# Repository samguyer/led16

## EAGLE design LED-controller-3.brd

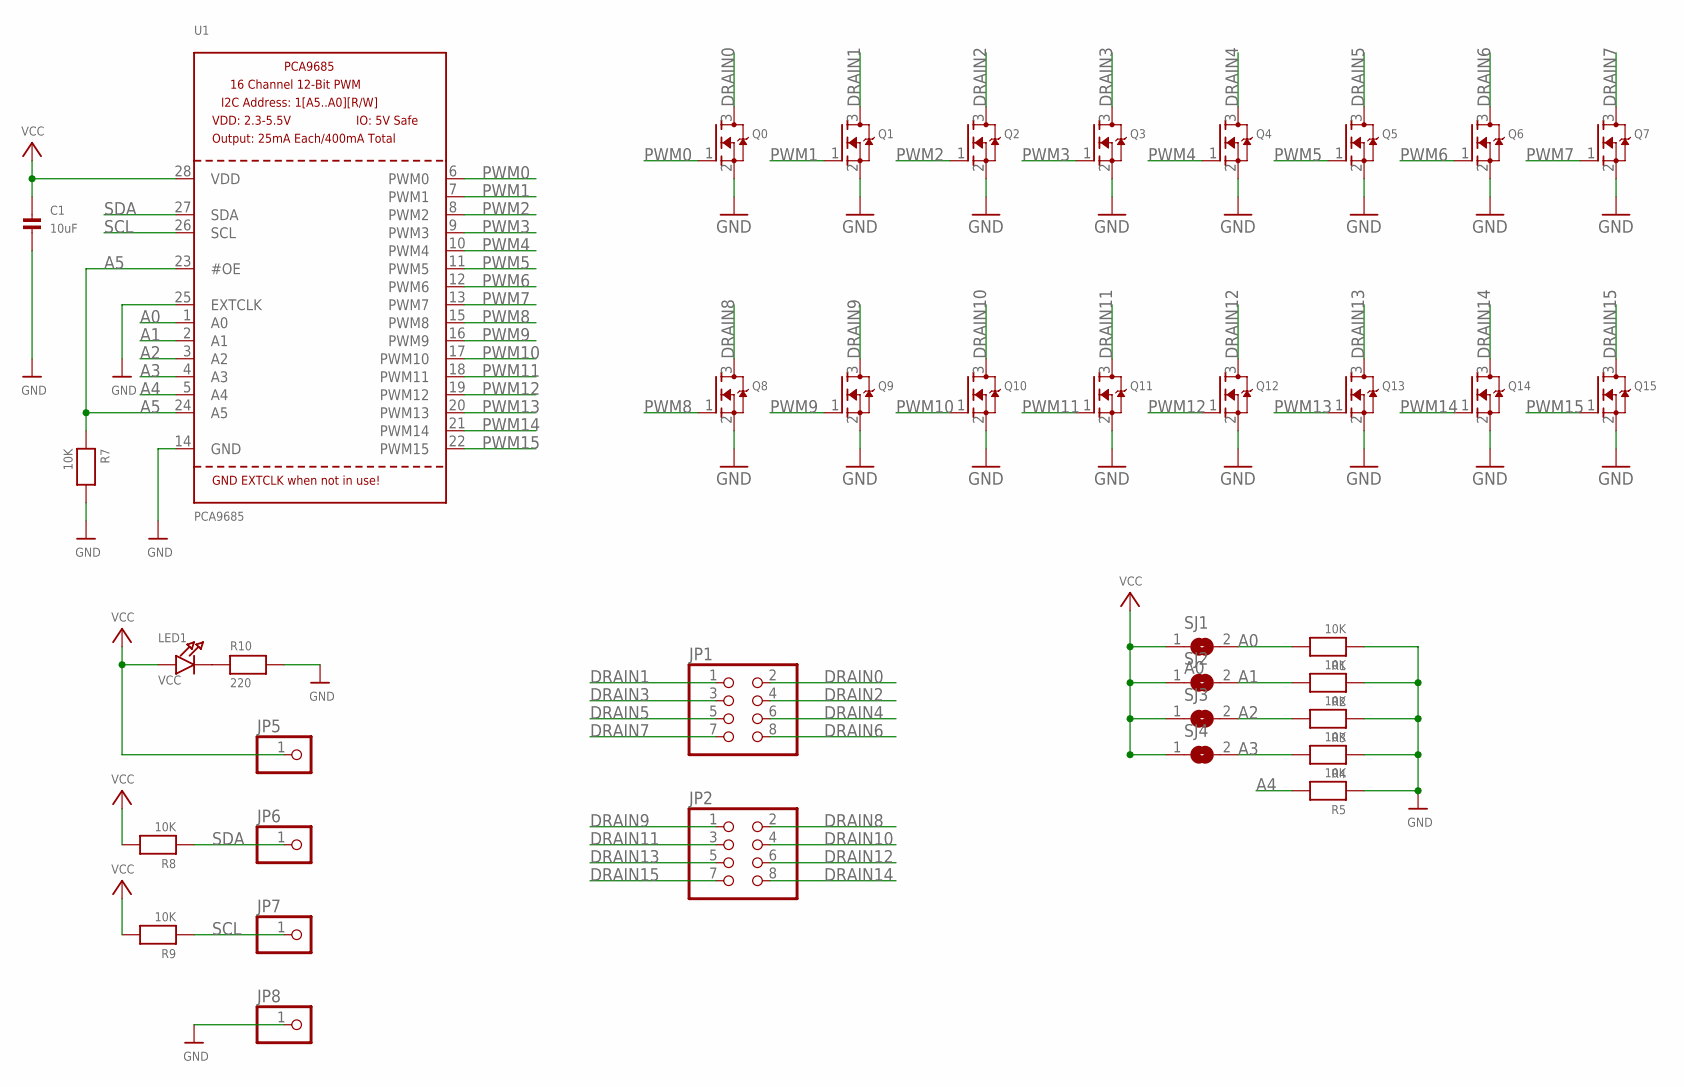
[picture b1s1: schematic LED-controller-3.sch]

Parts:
C1: 10uF; 0805
JP1, JP2: PINHD-2X4; 2X04
JP5, JP6, JP7, JP8: PINHD-1X1CB; 1X01-CLEANBIG
LED1: VCC; CHIPLED_0805
Q0, Q1, Q2, Q3, Q4, Q5, Q6, Q7, Q8, Q9, Q10, Q11, Q12, Q13, Q14, Q15: MOSFET-NREFLOW; SOT23
R1, R2, R3, R4, R5, R7, R8, R9: 10K; 0603
R10: 220; 0603
SJ1: A0; SJ
SJ2, SJ3, SJ4: SJ
U1: PCA9685; TSSOP28

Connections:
A0: R1.2, SJ1.2, U1.1 (A0)
A1: R2.2, SJ2.2, U1.2 (A1)
A2: R3.2, SJ3.2, U1.3 (A2)
A3: R4.2, SJ4.2, U1.4 (A3)
A4: R5.2, U1.5 (A4)
A5: R7.1, U1.23 (#OE), U1.24 (A5)
DRAIN0: JP1.2, Q0.3 (D)
DRAIN1: JP1.1, Q1.3 (D)
DRAIN2: JP1.4, Q2.3 (D)
DRAIN3: JP1.3, Q3.3 (D)
DRAIN4: JP1.6, Q4.3 (D)
DRAIN5: JP1.5, Q5.3 (D)
DRAIN6: JP1.8, Q6.3 (D)
DRAIN7: JP1.7, Q7.3 (D)
DRAIN8: JP2.2, Q8.3 (D)
DRAIN9: JP2.1, Q9.3 (D)
DRAIN10: JP2.4, Q10.3 (D)
DRAIN11: JP2.3, Q11.3 (D)
DRAIN12: JP2.6, Q12.3 (D)
DRAIN13: JP2.5, Q13.3 (D)
DRAIN14: JP2.8, Q14.3 (D)
DRAIN15: JP2.7, Q15.3 (D)
GND: C1.2, JP8.1, Q0.2 (S), Q1.2 (S), Q2.2 (S), Q3.2 (S), Q4.2 (S), Q5.2 (S), Q6.2 (S), Q7.2 (S), Q8.2 (S), Q9.2 (S), Q10.2 (S), Q11.2 (S), Q12.2 (S), Q13.2 (S), Q14.2 (S), Q15.2 (S), R1.1, R2.1, R3.1, R4.1, R5.1, R7.2, R10.2, U1.14 (GND), U1.25 (EXTCLK)
unnamed: LED1.C, R10.1
PWM0: Q0.1 (G), U1.6 (PWM0)
PWM1: Q1.1 (G), U1.7 (PWM1)
PWM2: Q2.1 (G), U1.8 (PWM2)
PWM3: Q3.1 (G), U1.9 (PWM3)
PWM4: Q4.1 (G), U1.10 (PWM4)
PWM5: Q5.1 (G), U1.11 (PWM5)
PWM6: Q6.1 (G), U1.12 (PWM6)
PWM7: Q7.1 (G), U1.13 (PWM7)
PWM8: Q8.1 (G), U1.15 (PWM8)
PWM9: Q9.1 (G), U1.16 (PWM9)
PWM10: Q10.1 (G), U1.17 (PWM10)
PWM11: Q11.1 (G), U1.18 (PWM11)
PWM12: Q12.1 (G), U1.19 (PWM12)
PWM13: Q13.1 (G), U1.20 (PWM13)
PWM14: Q14.1 (G), U1.21 (PWM14)
PWM15: Q15.1 (G), U1.22 (PWM15)
SCL: JP7.1, R9.1, U1.26 (SCL)
SDA: JP6.1, R8.1, U1.27 (SDA)
VCC: C1.1, JP5.1, LED1.A, R8.2, R9.2, SJ1.1, SJ2.1, SJ3.1, SJ4.1, U1.28 (VDD)

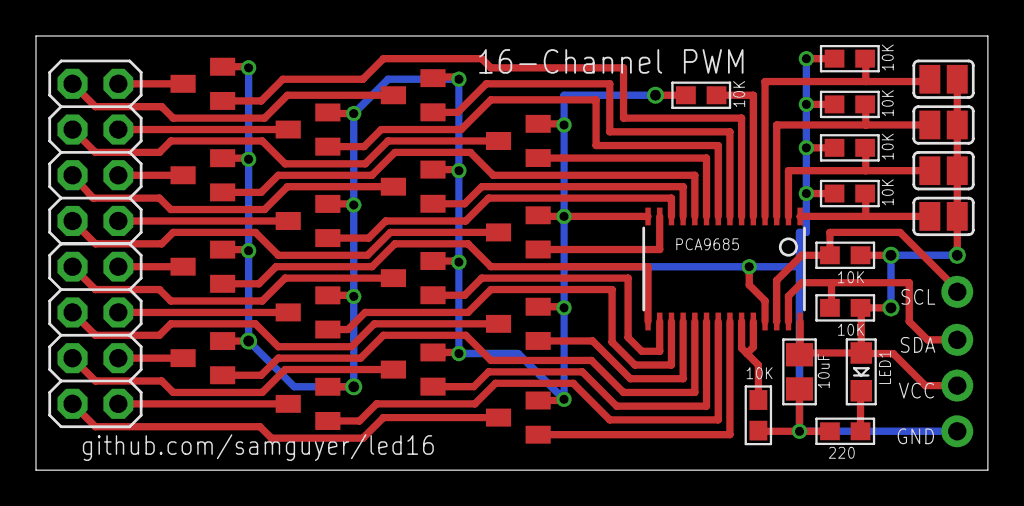
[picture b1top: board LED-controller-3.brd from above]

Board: 2 copper layers, 52.9 x 24.1 mm, 38 parts (0 on the bottom side), 43 nets.

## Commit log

2017-10-14 Added boards
